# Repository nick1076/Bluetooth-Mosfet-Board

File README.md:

# Bluetooth Mosfet Board
 Schematic, Code, and Documentation for a Bluetooth-controlled Mosfet board I am developing.

 ## Status
The Bluetooth Mosfet Board is currently still under development and I am currently focused on developing the custom PCB for the hardware. From there I will develop the software portion.

# Documentation

## Developing the PCB

To begin I drew up the schematic of the board I had in mind within KiCad. This board will be managed by an ATtiny 1614 microcontroller and will include a power indicator light, a heartbeat or code-based indication light, and of course a Mosfet (Thinking IRF510N). There will be SMD horizontal headers used to program and power the device, and also to jump certain outputs over to the Bluetooth board, which I am planning to us an HC-05 or HC-06 for.

## Routing Traces

After designing the PCB by laying out the schematic, I moved on to plot and route traces and componets as they would actually be milled on the board. I did so once again in KiCad and with some minor adjustments to the initial schematic I was able to get everything to route perfectly without the need for any jumps or 0 ohm resistors. The board from here can be milled and tested once software is developed.

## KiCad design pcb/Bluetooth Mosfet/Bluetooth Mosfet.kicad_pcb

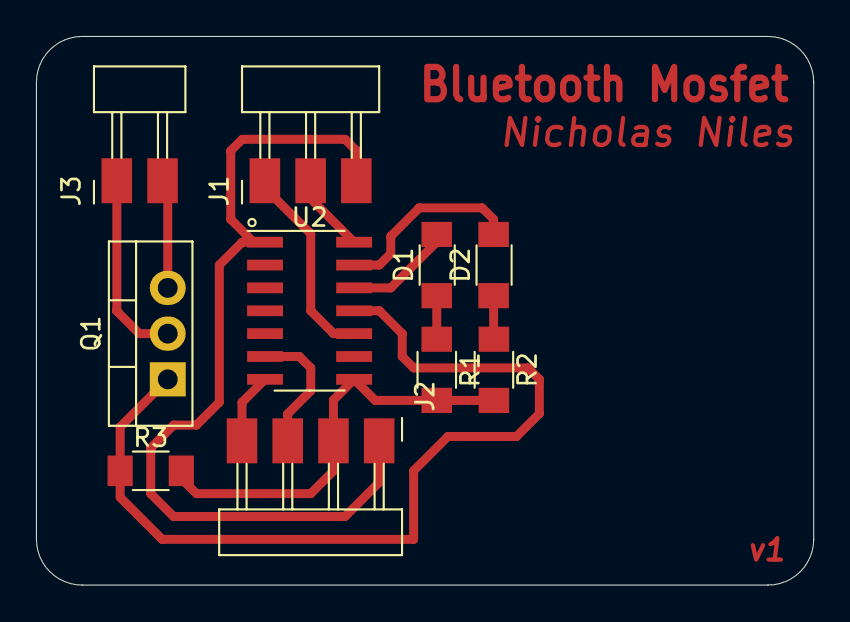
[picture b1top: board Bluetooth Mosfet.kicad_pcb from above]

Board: 2 copper layers, 43.2 x 30.5 mm, 10 parts (0 on the bottom side), 12 nets.

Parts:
D1, D2: LED; LED_1206
J1: 1x3 Header; PinHeader_1x03_P2.54mm_Horizontal_SMD
J2: 1x4 Header; PinHeader_1x04_P2.54mm_Horizontal_SMD
J3: 1x2 Header; PinHeader_1x02_P2.54mm_Horizontal_SMD
Q1: IRF510N; TO-220-3_Vertical
R1, R2: 330 Ohm; R_1206
R3: 10k Ohm; R_1206
U2: ATtiny 1614; SOIC-14_3.9x8.7mm_P1.27mm

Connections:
unnamed: D1.2 (A), U2.12 (PA2/D9)
unnamed: D1.1 (K), R1.1
unnamed: D2.2 (A), U2.13 (PA3/D10)
unnamed: D2.1 (K), R2.1
unnamed: J1.1, U2.10 (UPDI/PA0/D11)
unnamed: J1.2, J2.2, R1.2, R2.2, R3.2, U2.8 (PB1/SDA), U2.14 (GND)
unnamed: J1.3, J2.1, U2.1 (VCC)
unnamed: J2.3, U2.6 (PB3/RXD)
unnamed: J2.4, U2.7 (PB2/TXD)
unnamed: J3.1, Q1.2 (D)
unnamed: J3.2, Q1.3 (S)
unnamed: Q1.1 (G), R3.1, U2.11 (PA1/D8)

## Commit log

2024-06-17 Initial Upload & Schematic Implimentation
2024-06-17 Routed Traces for Milling
2024-06-17 Documentation & Schematic Wire Color Update
2024-06-17 Routing & Traces
2024-06-21 Schematic Updates
2024-06-24 Text update
